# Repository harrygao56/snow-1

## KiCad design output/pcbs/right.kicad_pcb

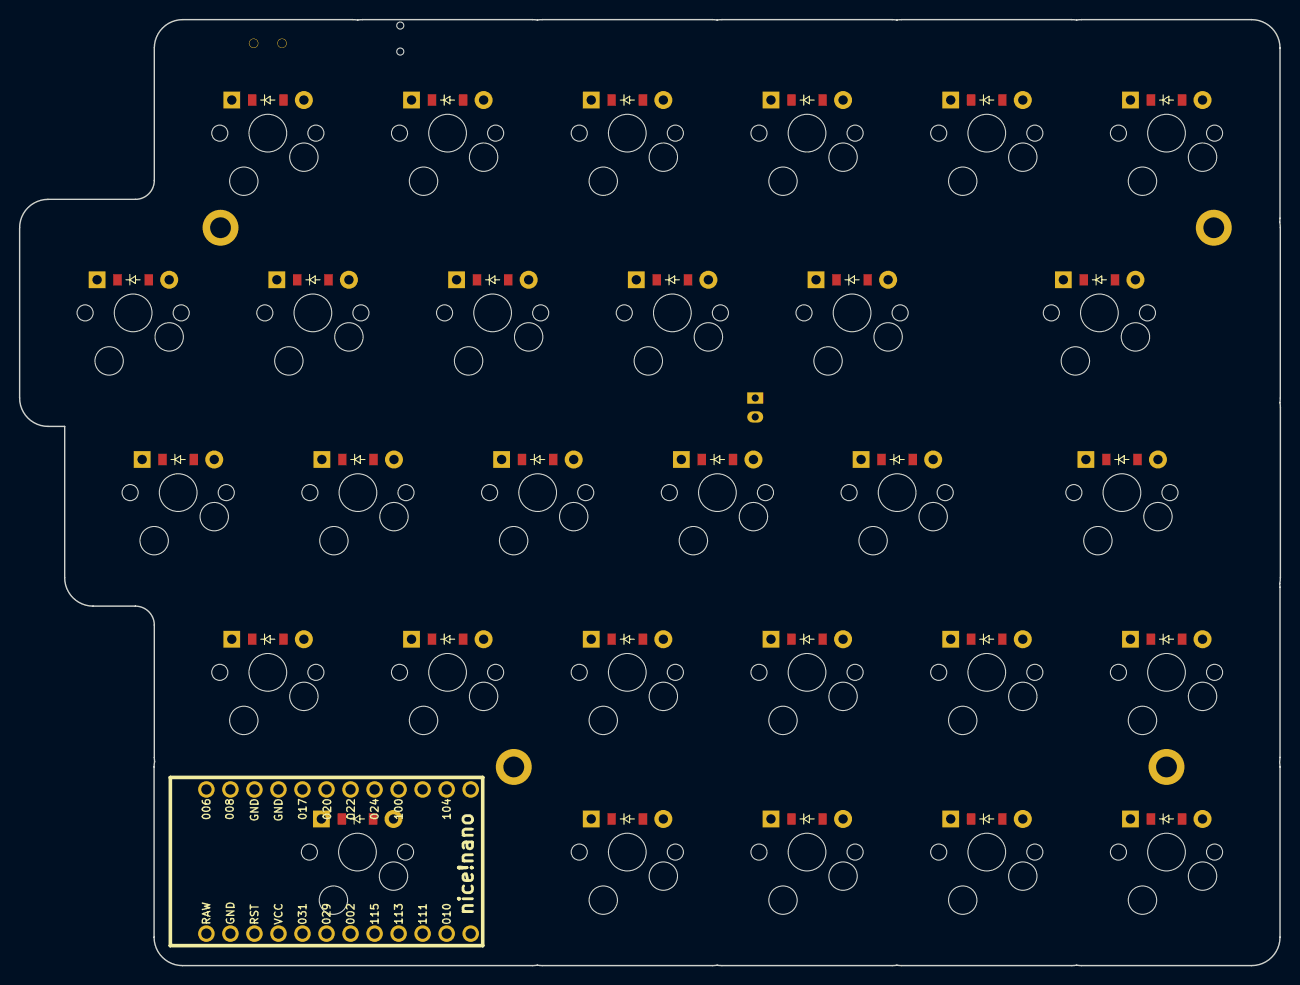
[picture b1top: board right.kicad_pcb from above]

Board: 2 copper layers, 133.3 x 100.0 mm, 66 parts (0 on the bottom side), 45 nets, no tracks yet.

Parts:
B1: Panasonic_EVQPUL_EVQPUC
D1, D2, D3, D4, D5, D6, D7, D8, D9, D10, D11, D12, D13, D14, D15, D16, D17, D18, D19, D20, D21, D22, D23, D24, D25, D26, D27, D28, D29: ComboDiode
H1, H2, H3, H4: mounting_hole
JST1: JST_PH_S2B-PH-K_02x2.00mm_Angled
MCU1: nice_nano
S1, S2, S3, S4, S5, S6, S7, S8, S9, S10, S11, S12, S13, S14, S15, S16, S17, S18, S19, S20, S21, S22, S23, S24, S25, S26, S27, S28, S29: MX
T1: SPDT_C128955

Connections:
GND: B1.1, JST1.2, MCU1.3, MCU1.4, MCU1.23
P006: MCU1.1, S1.1, S2.1
P008: MCU1.2, S3.1, S4.1, S5.1, S6.1
P009: MCU1.13, S17.1, S18.1, S19.1, S20.1, S21.1
P011: D7.1, D12.1, D17.1, D22.1, D27.1, MCU1.10
P024: MCU1.8, S22.1, S23.1, S24.1, S25.1, S26.1
P029: D6.1, D11.1, D16.1, D21.1, D26.1, D29.1, MCU1.19
P031: D2.1, D5.1, D10.1, D15.1, D20.1, D25.1, MCU1.20
P100: MCU1.9, S27.1, S28.1, S29.1
P104: D3.1, D8.1, D13.1, D18.1, D23.1, D28.1, MCU1.11
P106: D1.1, D4.1, D9.1, D14.1, D19.1, D24.1, MCU1.12
P111: MCU1.15, S12.1, S13.1, S14.1, S15.1, S16.1
P113: MCU1.16, S7.1, S8.1, S9.1, S10.1, S11.1
RAW: MCU1.24, T1.2
RST: B1.2, MCU1.22
c1_home: D1.2, S1.2
c1_top: D2.2, S2.2
c2_bottom: D3.2, S3.2
c2_home: D4.2, S4.2
c2_num: D6.2, S6.2
c2_top: D5.2, S5.2
c3_bottom: D8.2, S8.2
c3_home: D9.2, S9.2
c3_mod: D7.2, S7.2
c3_num: D11.2, S11.2
c3_top: D10.2, S10.2
c4_bottom: D13.2, S13.2
c4_home: D14.2, S14.2
c4_mod: D12.2, S12.2
c4_num: D16.2, S16.2
c4_top: D15.2, S15.2
c5_bottom: D18.2, S18.2
c5_home: D19.2, S19.2
c5_mod: D17.2, S17.2
c5_num: D21.2, S21.2
c5_top: D20.2, S20.2
c6_bottom: D23.2, S23.2
c6_home: D24.2, S24.2
c6_mod: D22.2, S22.2
c6_num: D26.2, S26.2
c6_top: D25.2, S25.2
c7_bottom: D28.2, S28.2
c7_mod: D27.2, S27.2
c7_num: D29.2, S29.2
pos: JST1.1, T1.1

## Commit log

2026-01-18 init
2026-01-19 Add project title to README
2026-01-21 config changes, route pcbs
2026-01-21 Add description to README for snow-1 keyboard
2026-02-09 case
2026-02-17 Simplify project title in README
    Removed the subtitle for the project.
